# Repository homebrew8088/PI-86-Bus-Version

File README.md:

# PI-86-Bus-Version
8088 V20 Raspberry Pi "hat"

\
\
This is a repository for my 8088 Raspberry Pi "hat" This is the 3rd version of this project and is quite different than previous versions. The intent was to achieve faster processing speeds by allowing the 8088 to run at its own speed. 

**Homepage**\
https://www.homebrew8088.com/

**Join the discussion group on Discord**\
https://discord.gg/AswNqwpRGP

**eBay store**\
http://www.ebay.com/sch/emil6190/m.html

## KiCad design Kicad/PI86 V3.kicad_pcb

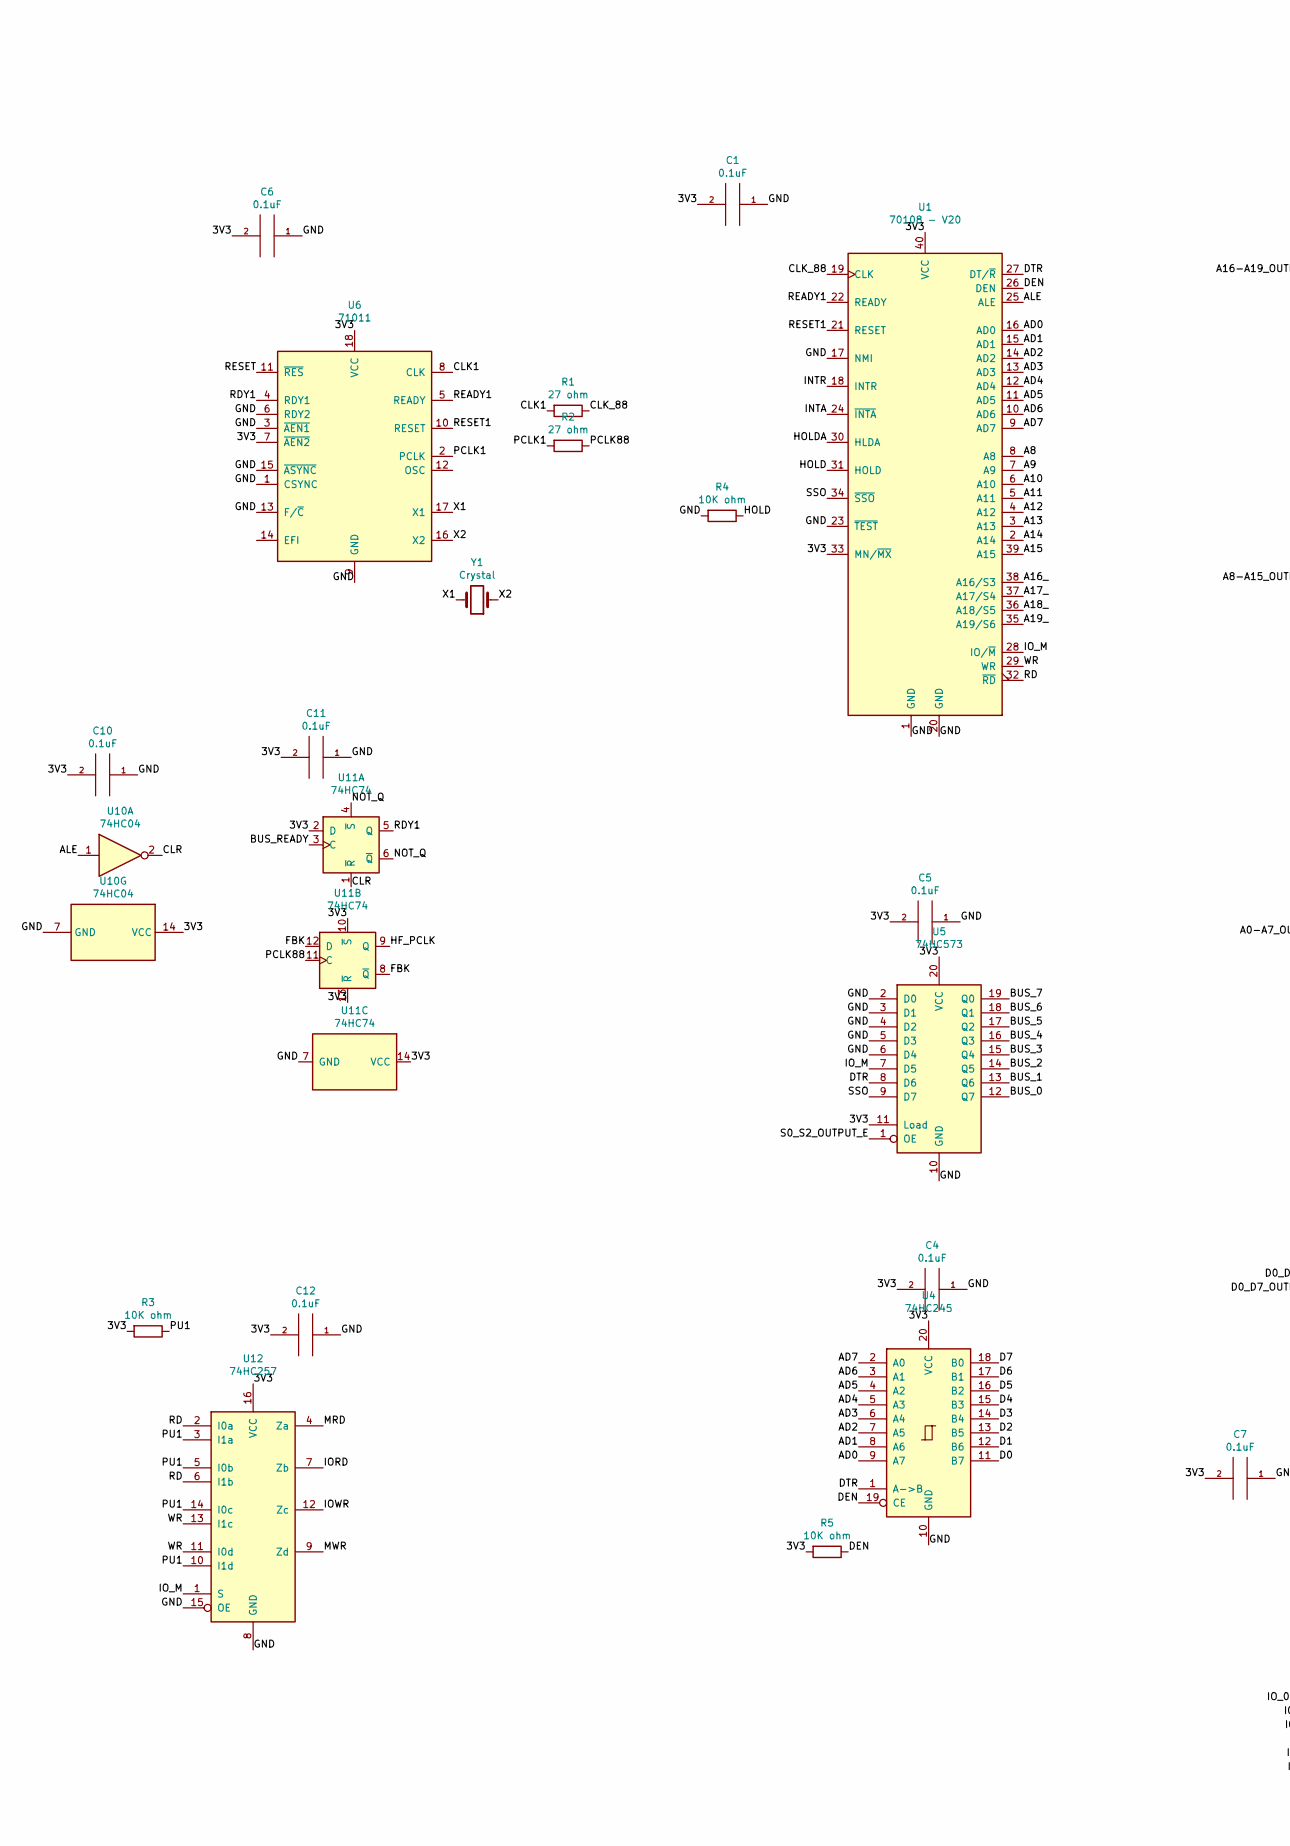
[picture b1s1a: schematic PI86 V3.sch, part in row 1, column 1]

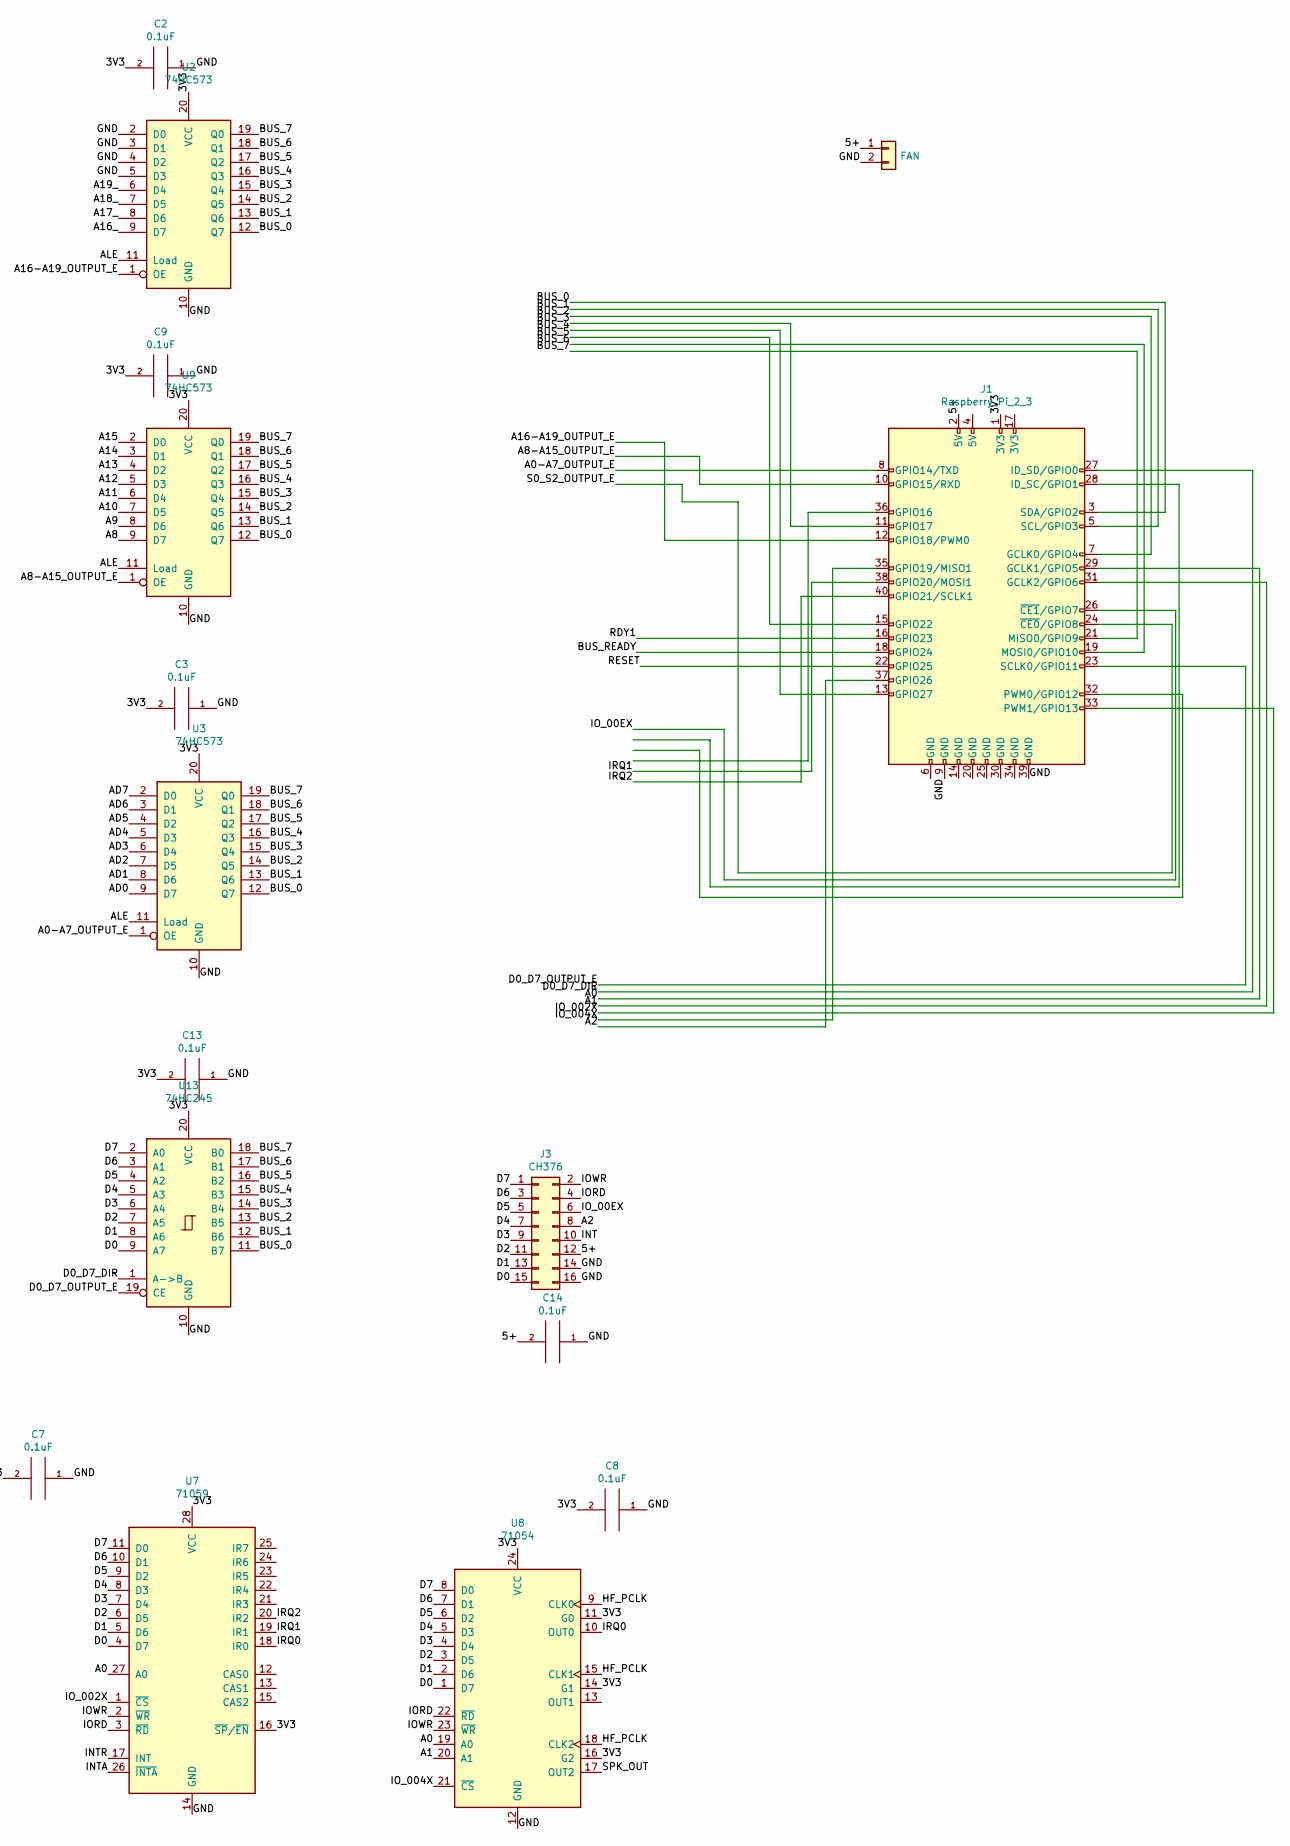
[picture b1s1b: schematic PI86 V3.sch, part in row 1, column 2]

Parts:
C1, C2, C3, C4, C5, C6, C7, C8, C9, C10, C11, C12, C13, C14: 0.1uF; C_Disc_D4.3mm_W1.9mm_P5.00mm
J1: Raspberry_Pi_2_3; PinHeader_2x20_P2.54mm_Vertical
J2: FAN; PinHeader_1x02_P2.54mm_Vertical
J3: CH376; PinHeader_2x08_P2.54mm_Vertical
R1, R2: 27 ohm; R_Axial_DIN0207_L6.3mm_D2.5mm_P10.16mm_Horizontal
R3, R4, R5: 10K ohm; R_Axial_DIN0207_L6.3mm_D2.5mm_P10.16mm_Horizontal
U1: 70108 - V20; DIP-40_W15.24mm
U2, U3, U5, U9: 74HC573; DIP-20_W7.62mm
U4, U13: 74HC245; DIP-20_W7.62mm
U6: 71011; DIP-18_W7.62mm
U7: 71059; DIP-28_W15.24mm
U8: 71054; DIP-24_W15.24mm
U10: 74HC04; DIP-14_W7.62mm
U11: 74HC74; DIP-14_W7.62mm
U12: 74HC257; DIP-16_W7.62mm
Y1: Crystal; Crystal_HC18-U_Vertical

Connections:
/3V3: C1.2, C2.2, C3.2, C4.2, C5.2, C6.2, C7.2, C8.2, C9.2, C10.2, C11.2, C12.2, C13.2, J1.1 (3V3), R3.2, R5.2, U1.33 (MN/~MX~), U1.40 (VCC), U2.20 (VCC), U3.20 (VCC), U4.20 (VCC), U5.11 (Load), U5.20 (VCC), U6.7 (~AEN2~), U6.18 (VCC), U7.16 (~SP~/~EN~), U7.28 (VCC), U8.11 (G0), U8.14 (G1), U8.16 (G2), U8.24 (VCC), U9.20 (VCC), U10.14 (VCC), U11.2 (D), U11.10 (~S), U11.13 (~R), U11.14 (VCC), U12.16 (VCC), U13.20 (VCC)
/5+: C14.2, J1.2 (5V), J2.1, J3.12
/A0: J1.29 (GCLK1/GPIO5), U7.27 (A0), U8.19 (A0)
/A0-A7_OUTPUT_E: J1.8 (GPIO14/TXD), U3.1 (OE)
/A1: J1.31 (GCLK2/GPIO6), U8.20 (A1)
/A2: J1.37 (GPIO26), J3.8
/A8: U1.8 (A8), U9.9 (D7)
/A8-A15_OUTPUT_E: J1.10 (GPIO15/RXD), U9.1 (OE)
/A9: U1.7 (A9), U9.8 (D6)
/A10: U1.6 (A10), U9.7 (D5)
/A11: U1.5 (A11), U9.6 (D4)
/A12: U1.4 (A12), U9.5 (D3)
/A13: U1.3 (A13), U9.4 (D2)
/A14: U1.2 (A14), U9.3 (D1)
/A15: U1.39 (A15), U9.2 (D0)
/A16-A19_OUTPUT_E: J1.12 (GPIO18/PWM0), U2.1 (OE)
/A16_: U1.38 (A16/S3), U2.9 (D7)
/A17_: U1.37 (A17/S4), U2.8 (D6)
/A18_: U1.36 (A18/S5), U2.7 (D5)
/A19_: U1.35 (A19/S6), U2.6 (D4)
/AD0: U1.16 (AD0), U3.9 (D7), U4.9 (A7)
/AD1: U1.15 (AD1), U3.8 (D6), U4.8 (A6)
/AD2: U1.14 (AD2), U3.7 (D5), U4.7 (A5)
/AD3: U1.13 (AD3), U3.6 (D4), U4.6 (A4)
/AD4: U1.12 (AD4), U3.5 (D3), U4.5 (A3)
/AD5: U1.11 (AD5), U3.4 (D2), U4.4 (A2)
/AD6: U1.10 (AD6), U3.3 (D1), U4.3 (A1)
/AD7: U1.9 (AD7), U3.2 (D0), U4.2 (A0)
/ALE: U1.25 (ALE), U2.11 (Load), U3.11 (Load), U9.11 (Load), U10.1
/BUS_0: J1.3 (SDA/GPIO2), U2.12 (Q7), U3.12 (Q7), U5.12 (Q7), U9.12 (Q7), U13.11 (B7)
/BUS_1: J1.5 (SCL/GPIO3), U2.13 (Q6), U3.13 (Q6), U5.13 (Q6), U9.13 (Q6), U13.12 (B6)
/BUS_2: J1.7 (GCLK0/GPIO4), U2.14 (Q5), U3.14 (Q5), U5.14 (Q5), U9.14 (Q5), U13.13 (B5)
/BUS_3: J1.11 (GPIO17), U2.15 (Q4), U3.15 (Q4), U5.15 (Q4), U9.15 (Q4), U13.14 (B4)
/BUS_4: J1.13 (GPIO27), U2.16 (Q3), U3.16 (Q3), U5.16 (Q3), U9.16 (Q3), U13.15 (B3)
/BUS_5: J1.15 (GPIO22), U2.17 (Q2), U3.17 (Q2), U5.17 (Q2), U9.17 (Q2), U13.16 (B2)
/BUS_6: J1.19 (MOSI0/GPIO10), U2.18 (Q1), U3.18 (Q1), U5.18 (Q1), U9.18 (Q1), U13.17 (B1)
/BUS_7: J1.21 (MISO0/GPIO9), U2.19 (Q0), U3.19 (Q0), U5.19 (Q0), U9.19 (Q0), U13.18 (B0)
/BUS_READY: J1.18 (GPIO24), U11.3 (C)
/CLK1: R1.2, U6.8 (CLK)
/CLK_88: R1.1, U1.19 (CLK)
/CLR: U10.2, U11.1 (~R)
/D0: J3.15, U4.11 (B7), U7.4 (D7), U8.1 (D7), U13.9 (A7)
/D0_D7_DIR: J1.27 (ID_SD/GPIO0), U13.1 (A->B)
/D0_D7_OUTPUT_E: J1.23 (SCLK0/GPIO11), U13.19 (CE)
/D1: J3.13, U4.12 (B6), U7.5 (D6), U8.2 (D6), U13.8 (A6)
/D2: J3.11, U4.13 (B5), U7.6 (D5), U8.3 (D5), U13.7 (A5)
/D3: J3.9, U4.14 (B4), U7.7 (D4), U8.4 (D4), U13.6 (A4)
/D4: J3.7, U4.15 (B3), U7.8 (D3), U8.5 (D3), U13.5 (A3)
/D5: J3.5, U4.16 (B2), U7.9 (D2), U8.6 (D2), U13.4 (A2)
/D6: J3.3, U4.17 (B1), U7.10 (D1), U8.7 (D1), U13.3 (A1)
/D7: J3.1, U4.18 (B0), U7.11 (D0), U8.8 (D0), U13.2 (A0)
/DEN: R5.1, U1.26 (DEN), U4.19 (CE)
/DTR: U1.27 (DT/~R~), U4.1 (A->B), U5.8 (D6)
/FBK: U11.8 (~Q), U11.12 (D)
/GND: C1.1, C2.1, C3.1, C4.1, C5.1, C6.1, C7.1, C8.1, C9.1, C10.1, C11.1, C12.1, C13.1, C14.1, J1.9 (GND), J1.39 (GND), J2.2, J3.14, J3.16, R4.2, U1.1 (GND), U1.17 (NMI), U1.20 (GND), U1.23 (~TEST~), U2.2 (D0), U2.3 (D1), U2.4 (D2), U2.5 (D3), U2.10 (GND), U3.10 (GND), U4.10 (GND), U5.2 (D0), U5.3 (D1), U5.4 (D2), U5.5 (D3), U5.6 (D4), U5.10 (GND), U6.1 (CSYNC), U6.3 (~AEN1~), U6.6 (RDY2), U6.9 (GND), U6.13 (F/~C~), U6.15 (~ASYNC~), U7.14 (GND), U8.12 (GND), U9.10 (GND), U10.7 (GND), U11.7 (GND), U12.8 (GND), U12.15 (OE), U13.10 (GND)
/HF_PCLK: U8.9 (CLK0), U8.15 (CLK1), U8.18 (CLK2), U11.9 (Q)
/HOLD: R4.1, U1.31 (HOLD)
/HOLDA: U1.30 (HLDA)
/INT: J3.10
/INTA: U1.24 (~INTA~), U7.26 (~INTA~)
/INTR: U1.18 (INTR), U7.17 (INT)
/IORD: J3.4, U7.3 (~RD~), U8.22 (~RD~), U12.7 (Zb)
/IOWR: J3.2, U7.2 (~WR~), U8.23 (~WR~), U12.12 (Zc)
/IO_00EX: J1.26 (~CE1~/GPIO7), J3.6
/IO_002X: J1.33 (PWM1/GPIO13), U7.1 (~CS~)
/IO_004X: J1.35 (GPIO19/MISO1), U8.21 (~CS~)
/IO_M: U1.28 (IO/~M~), U5.7 (D5), U12.1 (S)
/IRQ0: U7.18 (IR0), U8.10 (OUT0)
/IRQ1: J1.38 (GPIO20/MOSI1), U7.19 (IR1)
/IRQ2: J1.40 (GPIO21/SCLK1), U7.20 (IR2)
/MRD: U12.4 (Za)
/MWR: U12.9 (Zd)
/NOT_Q: U11.4 (~S), U11.6 (~Q)
/PCLK1: R2.2, U6.2 (PCLK)
/PCLK88: R2.1, U11.11 (C)
/PU1: R3.1, U12.3 (I1a), U12.5 (I0b), U12.10 (I1d), U12.14 (I0c)
/RD: U1.32 (~RD~), U12.2 (I0a), U12.6 (I1b)
/RDY1: J1.16 (GPIO23), U6.4 (RDY1), U11.5 (Q)
/READY1: U1.22 (READY), U6.5 (READY)
/RESET: J1.22 (GPIO25), U6.11 (~RES~)
/RESET1: U1.21 (RESET), U6.10 (RESET)
/S0_S2_OUTPUT_E: J1.24 (~CE0~/GPIO8), U5.1 (OE)
/SPK_OUT: U8.17 (OUT2)
/SSO: U1.34 (~SSO~), U5.9 (D7)
/WR: U1.29 (WR), U12.11 (I0d), U12.13 (I1c)
/X1: U6.17 (X1), Y1.2
/X2: U6.16 (X2), Y1.1

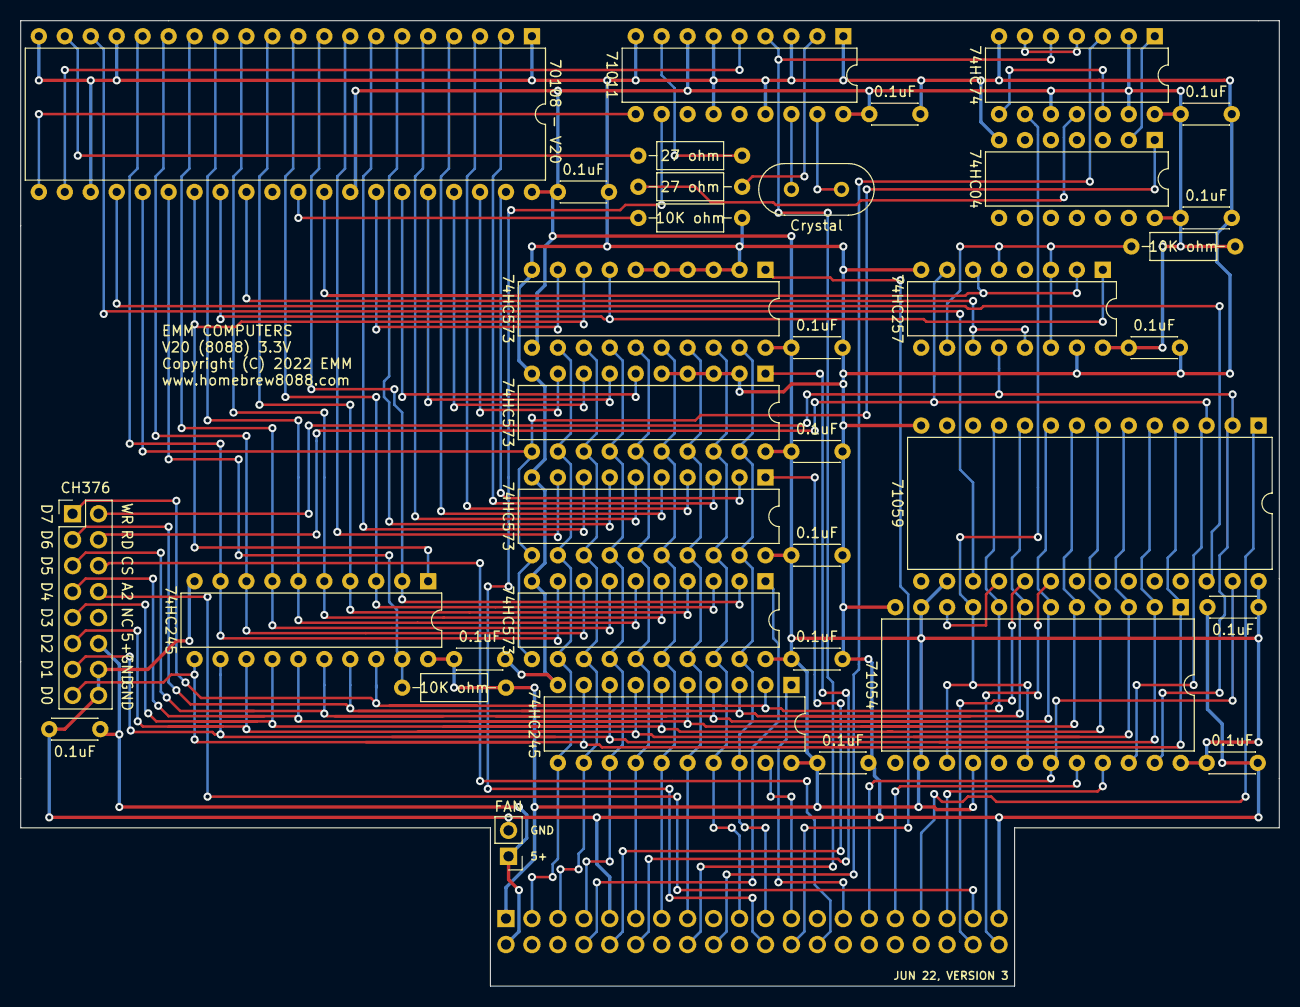
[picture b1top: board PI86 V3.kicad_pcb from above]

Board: 2 copper layers, 123.2 x 94.5 mm, 36 parts (1 on the bottom side), 82 nets.

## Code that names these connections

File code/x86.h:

#ifndef X86_H
#define X86_H


#define BUS_0   8
#define BUS_1   9
#define BUS_2   7
#define BUS_3   0
#define BUS_4   2
#define BUS_5   3
#define BUS_6   12
#define BUS_7   13

#define D0_D7_OUTPUT_E 	14
#define D0_D7_DIR 		30
#define PIN_A0			21
#define PIN_A1			22
#define PORT_20_CS		23	
#define PORT_40_CS		24
#define PIN_A2			25

#define A0_A7_OUTPUT_E	15
#define A8_A15_OUTPUT_E	16
#define A16_A19_OUTPUT_E 1

#define READY			4
#define BUS_READY		5
#define RESET			6

#define S0_S2_OUTPUT_E	10
#define PORT_E0_CS		11

#define IRQ1			28
#define IRQ2			29


#include <wiringPi.h>
#include <string>
#include <thread>
#include <unistd.h>
#include <fstream> 

using namespace std;

static bool Stop_Flag;


void Reset();	
void Start();
void Load_Bios(string Bios_file);
//Memory
void Write_Memory_Array(unsigned long long int Address, char code_for_8088[], int Length);
void Read_Memory_Array(unsigned long long int Address, char* char_Array, int Length);
void Write_Memory_Byte(unsigned long long int Address, char byte_for_8088);
char Read_Memory_Byte(unsigned long long int Address);		
void Write_Memory_Word(unsigned long long int Address, unsigned short int word_for_8088);
//IO

void Write_IO_Byte(unsigned long long int Address, char byte_for_8088);
char Read_IO_Byte(unsigned long long int Address);
void Write_IO_Word(unsigned long long int Address, unsigned short int word_for_8088);

//INT


#endif

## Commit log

2022-06-06 Initial push
2022-07-20 Update fp-info-cache
2022-07-20 added bios code
2022-07-20 rename file

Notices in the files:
Kicad/PI86 V3.kicad_pcb:
Copyright (C) 2022 EMM
